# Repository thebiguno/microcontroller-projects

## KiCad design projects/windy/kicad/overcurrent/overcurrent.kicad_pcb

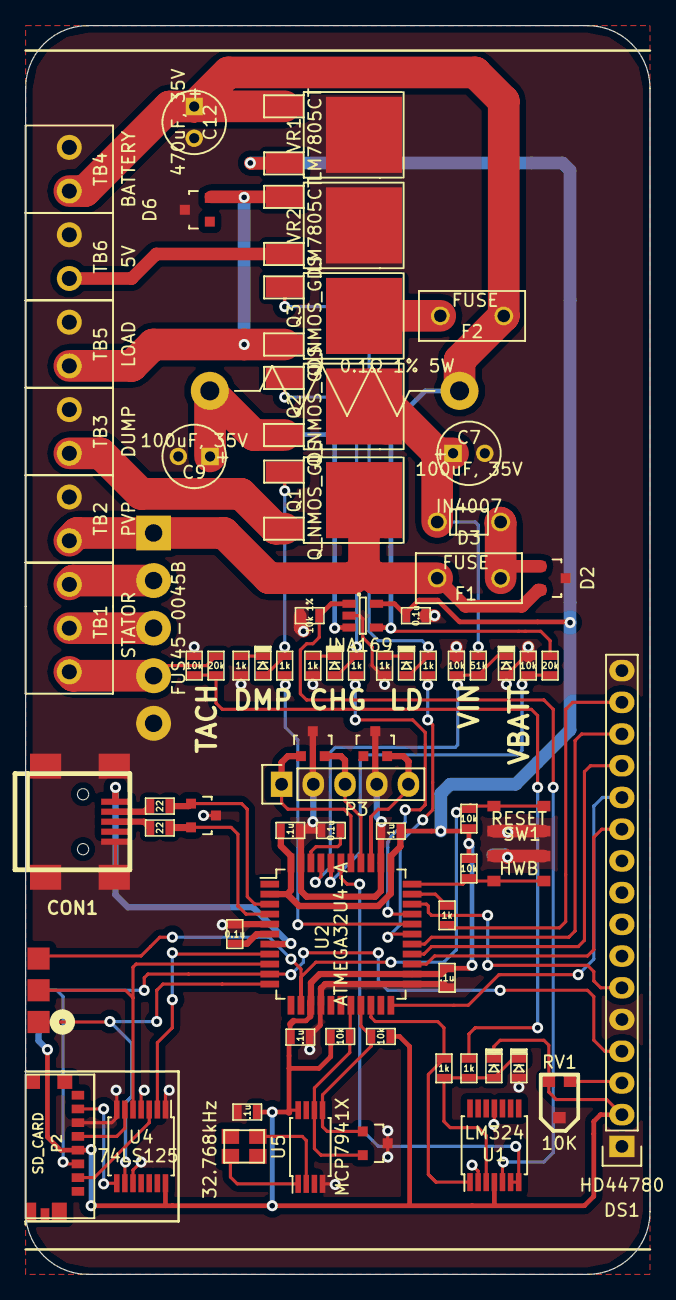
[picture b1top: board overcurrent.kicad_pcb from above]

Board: 2 copper layers, 50.0 x 100.0 mm, 75 parts (0 on the bottom side), 61 nets.

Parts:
BR1: FUS45-0045B; i4-PAC-5
C2, C3, C10: 0.1u; SM0603_VALUE
C4, C5, C6, C8, C11: .1u; SM0603_VALUE
C7, C9: 100uF, 35V; C1V5
C12: 470uF, 35V; C1V5
CON1: USB-MINI-B; USB_MINI_B_fixed
D1, D4, D5: LED; SM0603_DIODE
D2, D6, D7, D8, D9, D10: TVS; SOT-23
D3: IN4007; D2
D11, D12: DSCHSMALL; SM0603_DIODE
D13: ZENERsmall; SM0603_DIODE
DS1: HD44780; Pin_Header_Straight_1x16
F1, F2: FUSE; Fuse_TE5_Littlefuse-395Series
P1: ISP; ISP_EDGE
P2: SD_CARD; 475710001
P3: ENCODER; Pin_Header_Straight_1x05
Q1, Q2, Q3: Q_NMOS_GDS; DPAK-2
R1, R17: 20k; SM0603_VALUE
R2, R5, R9, R12, R13, R14, R18: 10k; SM0603_VALUE
R3, R4: 22; SM0603_VALUE
R6, R7, R10, R11, R19, R20, R21, R22, R23: 1k; SM0603_VALUE
R8: 51k; SM0603_VALUE
R15: 0.1Ω 1% 5W; RESISTOR_POWER
R16: 10k 1%; SM0603_VALUE
RV1: 10K; POTENTIOMETER_SMD
SW1: RESET; sw_42_32
SW2: HWB; sw_42_32
TB1: STATOR; 3.5x3
TB2: PVP; 3.5x2
TB3: DUMP; 3.5x2
TB4: BATTERY; 3.5x2
TB5: LOAD; 3.5x2
TB6: 5V; 3.5x2
U1: LM324; TSSOP-14_4.4x5mm_Pitch0.65mm
U2: ATMEGA32U4-A; TQFP-44_10x10mm_Pitch0.8mm
U3: INA169; SOT-23-5
U4: 74LS125; TSSOP-14_4.4x5mm_Pitch0.65mm
U5: MCP7941X; TSSOP-8_4.4x3mm_Pitch0.65mm
VR1, VR2: LM7805CT; DPAK-2
X1: 32.768kHz; crystal_FA238-TSX3225

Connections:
/AC1: BR1.4, R1.2, TB1.1
/AC2: BR1.3, TB1.2
/AC3: BR1.2, TB1.3
/BATTERY: C12.1, F2.1, R15.1, R17.1, TB4.1, U3.4, VR1.1
/CHARGE_SW: R11.2, U2.30
/CURR: U1.6, U1.7, U2.39
/D4: DS1.11, U2.25
/D5: DS1.12, U2.22
/D6: DS1.13, U2.26
/D7: DS1.14, U2.27
/D+: D10.2, R3.1, U2.4
/D-: D10.1, R4.1, U2.3
/DUMP_LOAD: Q1.3, TB3.1
/DUMP_SW: R7.2, U2.29
/ENC_A: D8.1, P3.1, U2.38
/ENC_B: D8.2, P3.3, U2.37
/ENC_SW: D7.2, P3.5, U2.36
/FILTERED_SOURCE: C7.1, D3.2, Q2.2, R8.1
/FUSED_LOAD: F2.2, Q3.2
/FUSED_SOURCE: D2.1, D3.1, F1.2
/LCD_BL: R22.2, U2.32
/LCD_E: DS1.6, U2.31
/LOAD_SW: R20.2, U2.28
/MISO: P1.1, U2.11, U4.9
/MOSI: DS1.4, P1.4, P2.3, U2.10
/REGULATED_LOAD: TB6.1, VR2.3
/RESET: P1.5, R5.2, SW1.2, U2.13
/SCL: D9.2, R12.1, U2.18, U5.6
/SCLK: P1.3, U2.9, U4.5
/SDA: D9.1, R13.1, U2.19, U5.5
/SD_CS: U2.8, U4.2
/SOURCE: BR1.1, D2.2, F1.1, Q1.2, TB2.1
/SWITCHED_LOAD: D6.2, Q3.3, TB5.1, VR2.1
/SWITCHED_SOURCE: C9.1, Q2.3, R15.2, U3.3
/TACH: R23.1, U1.1, U2.20
/VBATT: R17.2, R18.1, U2.40
/VBUS: CON1.1, U2.7
/VIN: D13.2, R8.2, R9.1, U2.41
GND: BR1.5, C2.1, C3.1, C4.2, C5.2, C6.2, C7.2, C8.2, C9.2, C10.2, C11.2, C12.2, CON1.5, CON1.6, CON1.7, CON1.8, CON1.9, D2.3, D6.3, D7.3, D8.3, D9.3, D10.3, D12.1, D13.1, DS1.1, DS1.5, DS1.16, P1.6, P2.6, P3.2, P3.4, R2.2, R6.2, R9.2, R10.2, R16.2, R18.2, R19.2, RV1.3, SW1.1, SW2.2, TB2.2, TB3.2, TB4.2, TB5.2, TB6.2, U1.2, U1.11, U2.5, U2.15, U2.23, U2.35, U2.43, U3.2, U4.1, U4.4, U4.7, U4.10, U5.4, VR1.2, VR2.2
unnamed: C2.2, U2.6
unnamed: C3.2, U2.42
unnamed: CON1.2, R4.2
unnamed: CON1.3, R3.2
unnamed: D1.1, Q1.1, R7.1
unnamed: D1.2, R6.1
unnamed: D4.1, Q2.1, R11.1
unnamed: D4.2, R10.1
unnamed: D5.1, Q3.1, R20.1
unnamed: D5.2, R19.1
unnamed: D11.1, D12.2, R21.1, R23.2, U1.3
unnamed: DS1.3, RV1.2
unnamed: DS1.15, R22.1
unnamed: P2.2, U4.3
unnamed: P2.5, U4.6
unnamed: P2.7, U4.8
unnamed: R1.1, R2.1, R21.2
unnamed: R14.1, SW2.1, U2.33
unnamed: R16.1, U1.5, U3.1
unnamed: U5.1, X1.1
unnamed: U5.2, X1.2
VCC: C4.1, C5.1, C6.1, C8.1, C10.1, C11.1, D11.2, DS1.2, P1.2, P2.4, R5.1, R12.2, R13.2, R14.2, RV1.1, U1.4, U2.2, U2.14, U2.24, U2.34, U2.44, U3.5, U4.14, U5.8, VR1.3
